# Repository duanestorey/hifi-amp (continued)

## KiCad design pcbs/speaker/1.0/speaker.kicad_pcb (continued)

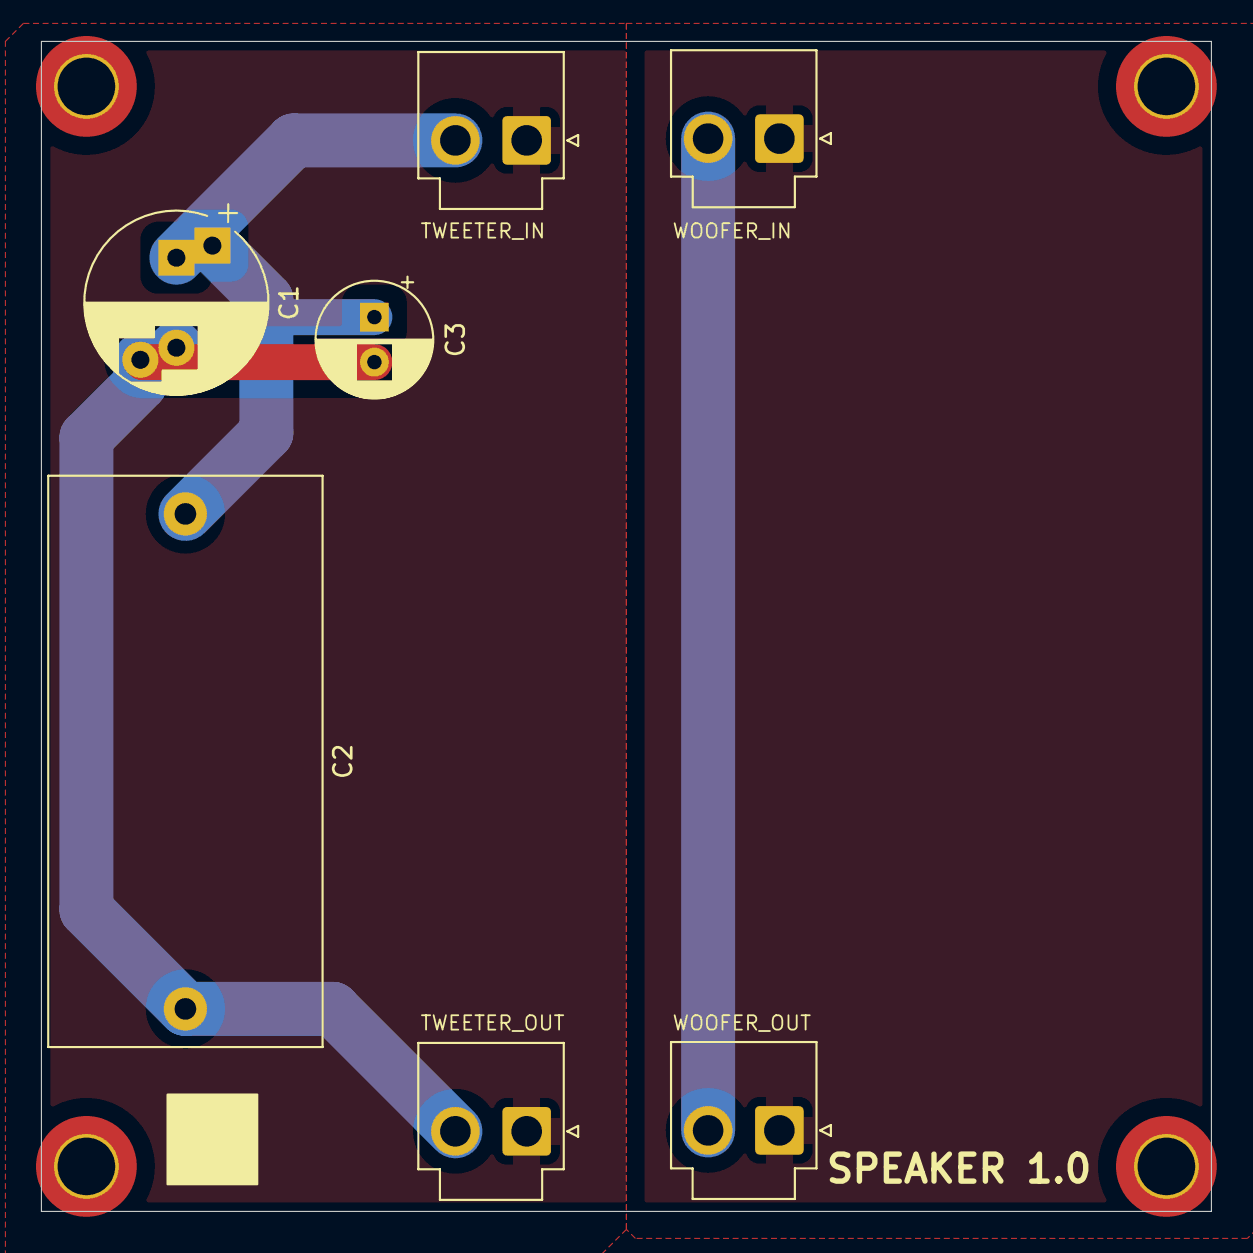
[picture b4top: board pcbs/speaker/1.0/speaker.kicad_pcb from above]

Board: 2 copper layers, 65.0 x 65.0 mm, 11 parts (0 on the bottom side), 5 nets.

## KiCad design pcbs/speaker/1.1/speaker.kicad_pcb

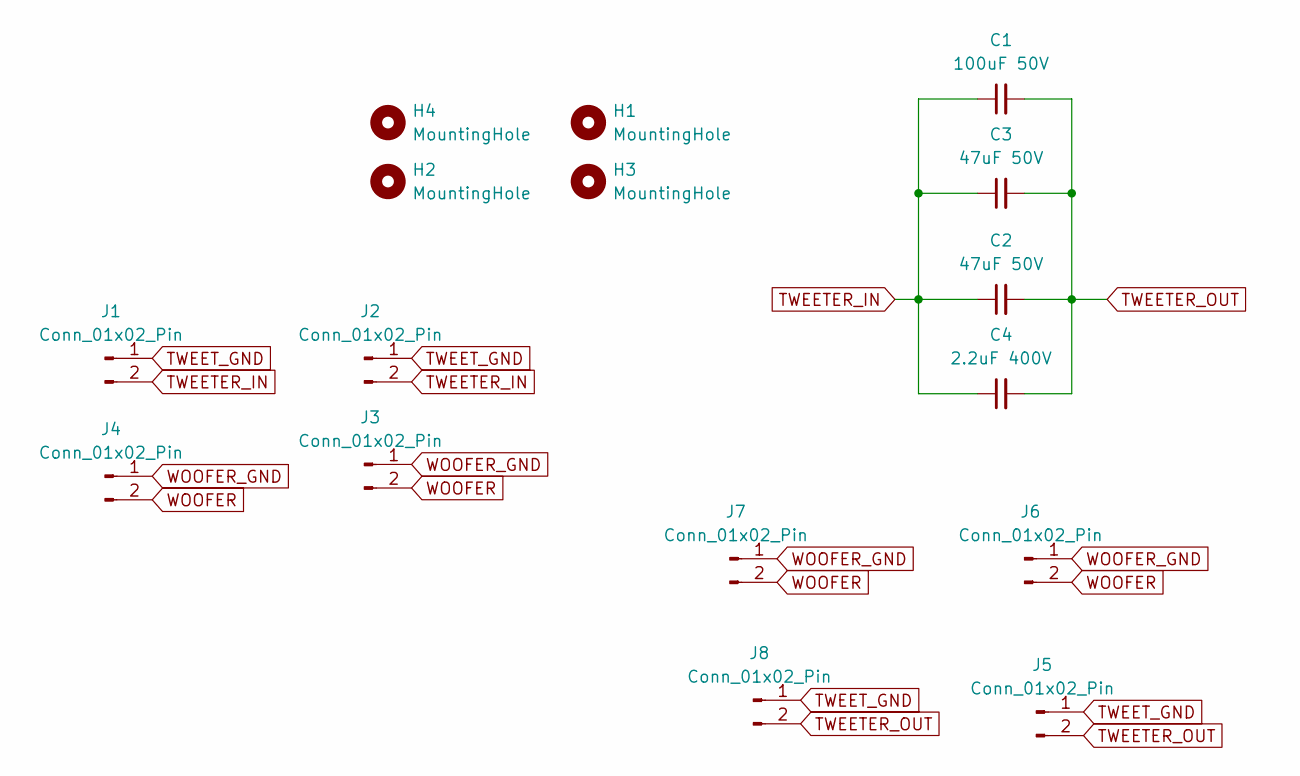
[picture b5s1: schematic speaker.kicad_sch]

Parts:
C1: 100uF 50V; CP_Radial_D12.5mm_P7.50mm
C2, C3: 47uF 50V; CP_Radial_D10.0mm_P5.00mm_P7.50mm
C4: 2.2uF 400V; C_Rect_L31.5mm_W15.0mm_P27.50mm_MKS4
H1, H2, H3, H4: MountingHole; MountingHole_3.2mm_M3_DIN965_Pad_TopBottom
J1, J4, J5, J6: Conn_01x02_Pin; TerminalBlock_Phoenix_PT-1,5-2-5.0-H_1x02_P5.00mm_Horizontal
J2, J3, J7, J8: Conn_01x02_Pin; JST_VH_B2P-VH-B_1x02_P3.96mm_Vertical

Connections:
TWEETER_IN: C1.1, C2.1, C3.1, C4.1, J1.2, J2.2
TWEETER_OUT: C1.2, C2.2, C3.2, C4.2, J5.2, J8.2
TWEET_GND: J1.1, J2.1, J5.1, J8.1
WOOFER: J3.2, J4.2, J6.2, J7.2
WOOFER_GND: J3.1, J4.1, J6.1, J7.1

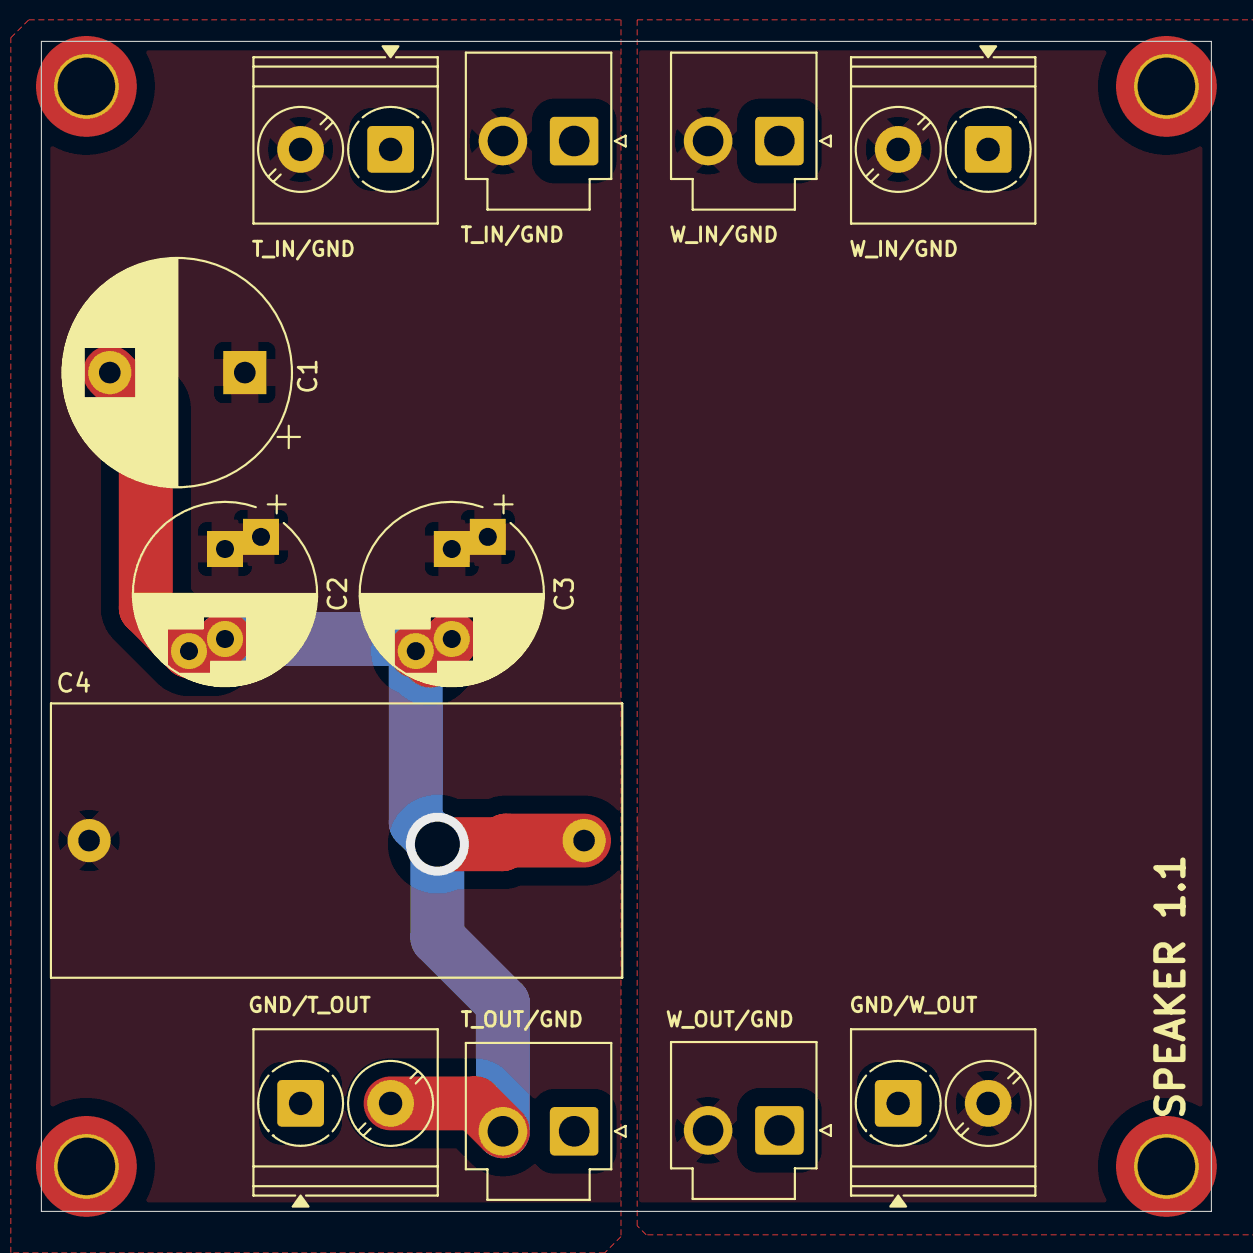
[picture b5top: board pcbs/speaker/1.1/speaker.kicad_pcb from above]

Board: 2 copper layers, 65.0 x 65.0 mm, 16 parts (0 on the bottom side), 5 nets.

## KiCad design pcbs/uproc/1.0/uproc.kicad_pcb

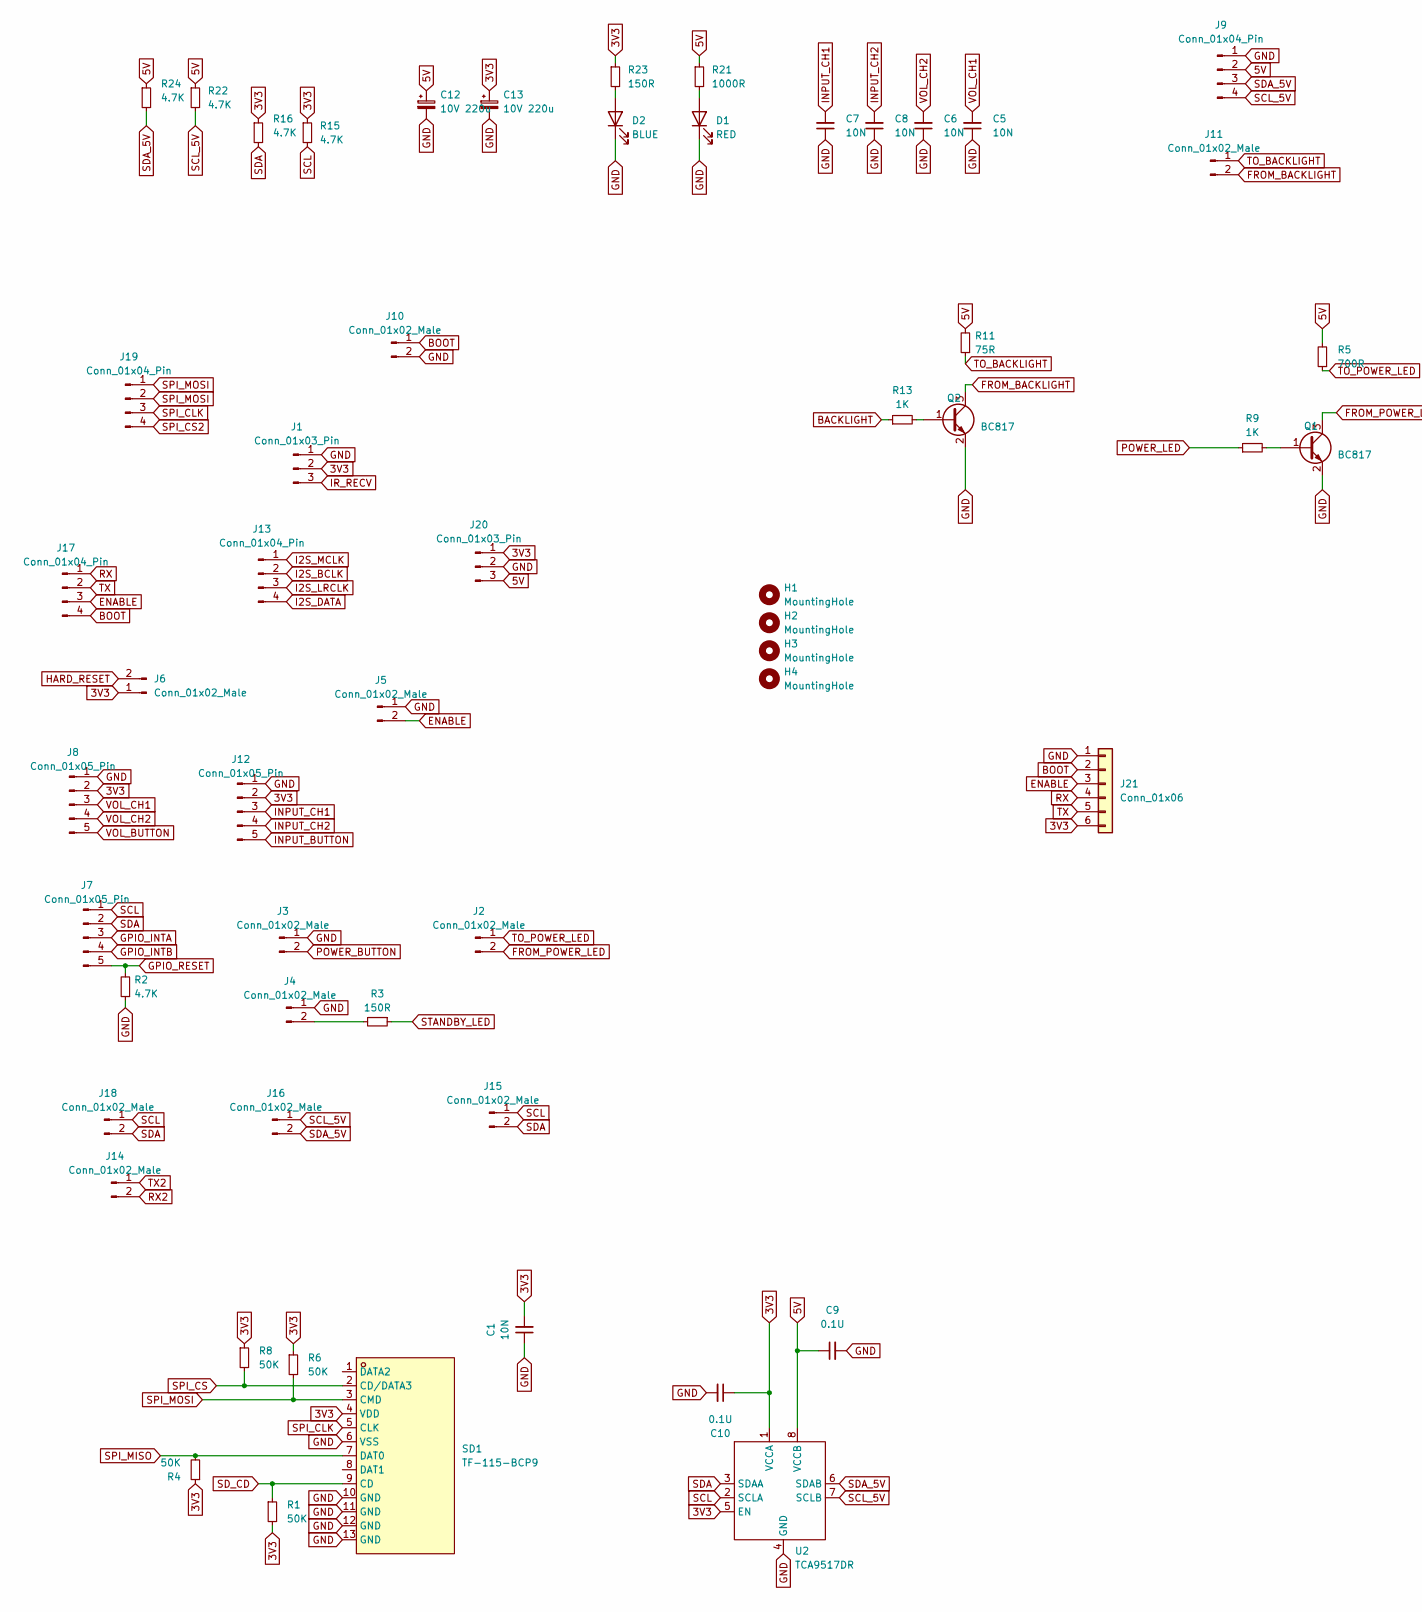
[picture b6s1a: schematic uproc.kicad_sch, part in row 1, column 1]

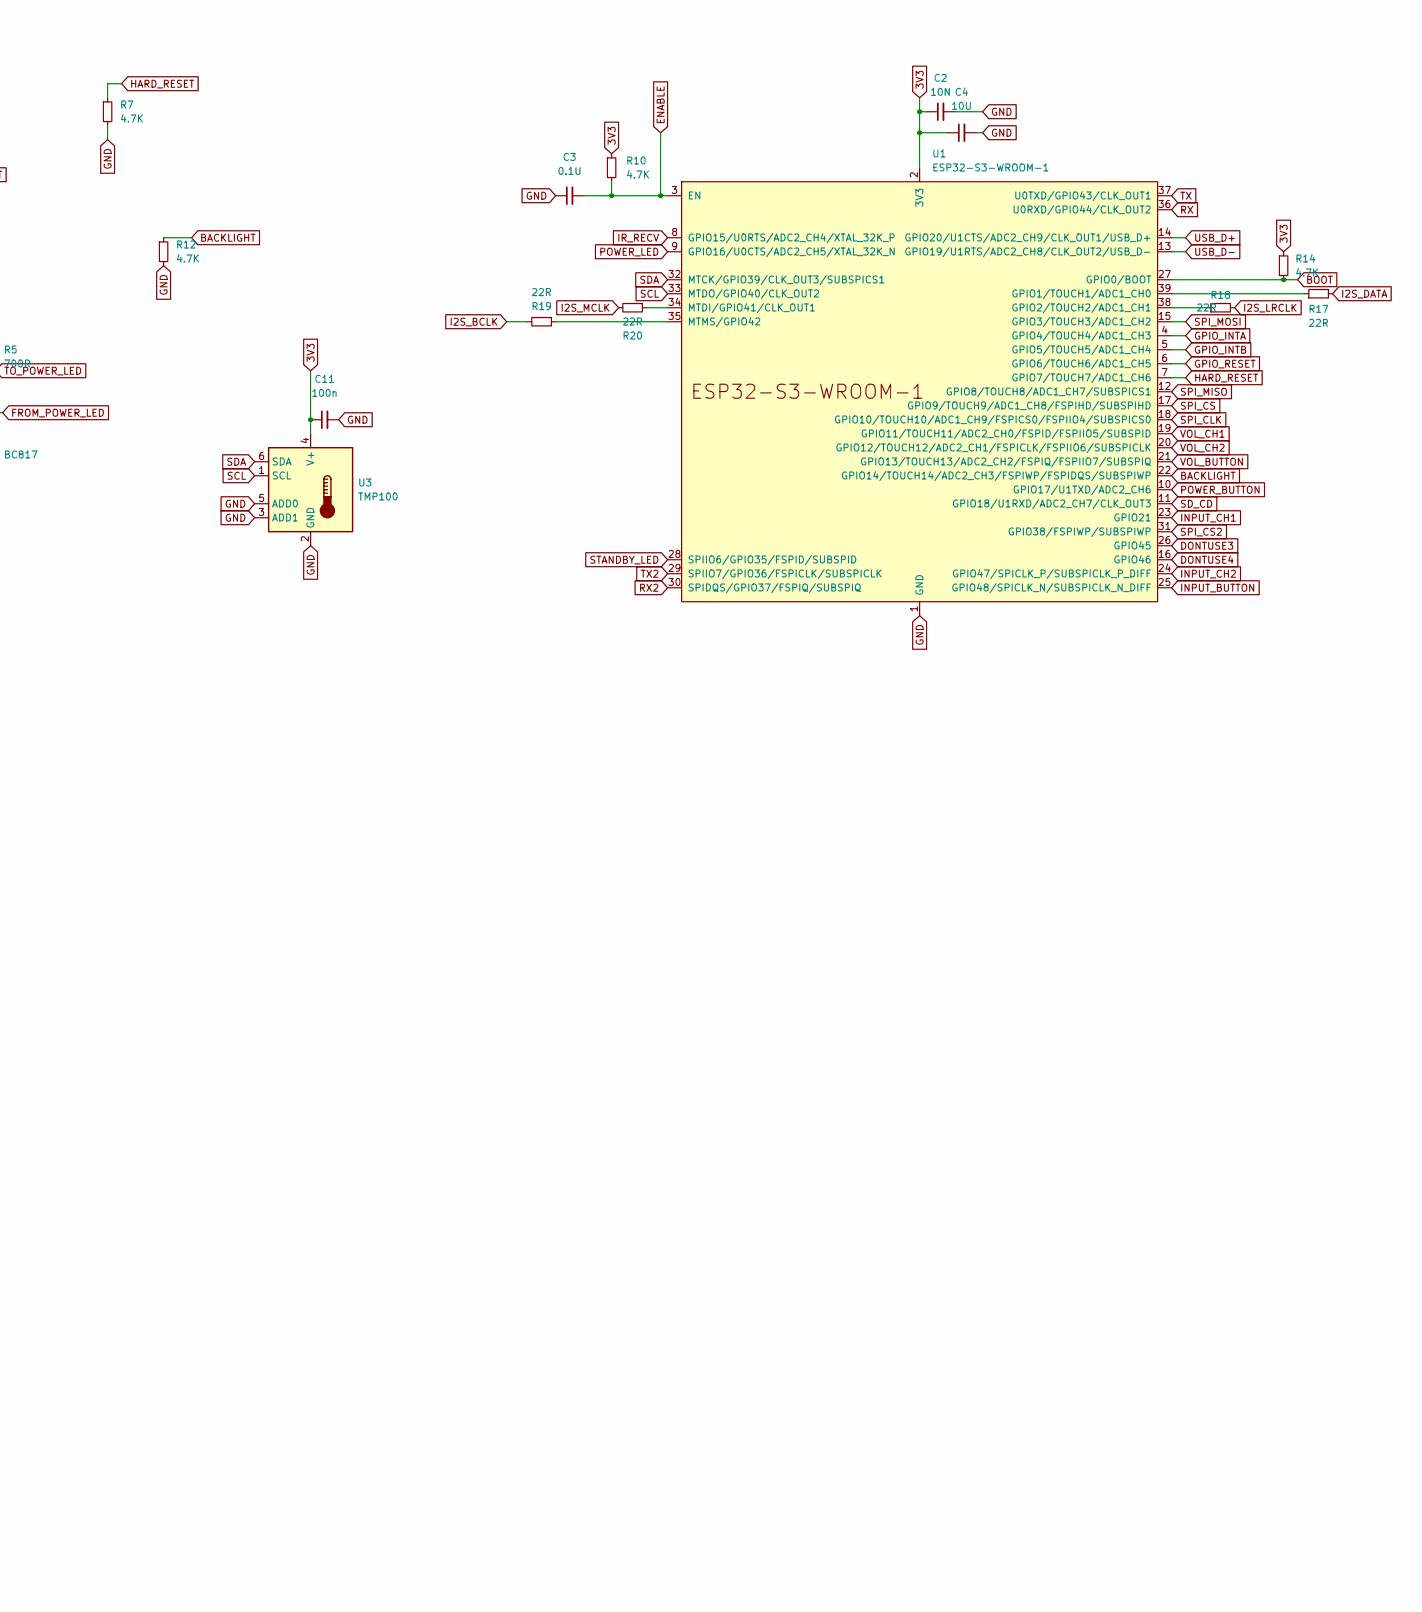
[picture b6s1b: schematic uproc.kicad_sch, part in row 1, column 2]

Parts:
C1, C2: 10N; C_0805_2012Metric_Pad1.18x1.45mm_HandSolder
C3, C9, C10: 0.1U; C_0805_2012Metric_Pad1.18x1.45mm_HandSolder
C4: 10U; C_1206_3216Metric_Pad1.33x1.80mm_HandSolder
C5, C6, C7, C8: 10N; C_0603_1608Metric_Pad1.08x0.95mm_HandSolder
C11: 100n; C_0805_2012Metric_Pad1.18x1.45mm_HandSolder
C12, C13: 10V 220u; CP_Radial_D6.3mm_P2.50mm
D1: RED; LED_0603_1608Metric; LCSC XL-1608UBC-04
D2: BLUE; LED_0603_1608Metric; LCSC NCD0603R1
H1, H2, H3, H4: MountingHole; MountingHole_3.2mm_M3_DIN965_Pad_TopOnly
J1, J20: Conn_01x03_Pin; JST_PH_B3B-PH-K_1x03_P2.00mm_Vertical
J2, J3, J4, J5, J11, J14, J15, J16, J18: Conn_01x02_Male; JST_PH_B2B-PH-K_1x02_P2.00mm_Vertical
J6, J10: Conn_01x02_Male; PinHeader_1x02_P2.54mm_Vertical
J7, J8, J12: Conn_01x05_Pin; JST_PH_B5B-PH-K_1x05_P2.00mm_Vertical
J9, J13, J17, J19: Conn_01x04_Pin; JST_PH_B4B-PH-K_1x04_P2.00mm_Vertical
J21: Conn_01x06; PinHeader_1x06_P2.54mm_Vertical
Q1, Q2: BC817; TSOT-23; Mouser 637-BC817K-40
R1, R4, R6, R8: 50K; R_0603_1608Metric_Pad0.98x0.95mm_HandSolder
R2, R7, R10, R12, R14, R15, R16, R22, R24: 4.7K; R_0603_1608Metric_Pad0.98x0.95mm_HandSolder
R3, R23: 150R; R_0603_1608Metric_Pad0.98x0.95mm_HandSolder
R5: 700R; R_0603_1608Metric_Pad0.98x0.95mm_HandSolder
R9, R13: 1K; R_0603_1608Metric_Pad0.98x0.95mm_HandSolder
R11: 75R; R_0603_1608Metric_Pad0.98x0.95mm_HandSolder
R17, R18, R19, R20: 22R; R_0603_1608Metric; Mouser 603-RT0805FRE0722RL
R21: 1000R; R_0603_1608Metric_Pad0.98x0.95mm_HandSolder
SD1: TF-115-BCP9; TF-SMD_TF-115-BCP9; LCSC Part C720505
U1: ESP32-S3-WROOM-1
U2: TCA9517DR; SOIC-8_3.9x4.9mm_P1.27mm; Mouser 595-TCA9517DR
U3: TMP100; SOT-23-6

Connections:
3V3: C1.2, C2.1, C4.1, C10.1, C11.1, C13.1, J1.2, J6.1, J8.2, J12.2, J20.1, J21.6, R1.2, R4.1, R6.1, R8.1, R10.1, R14.1, R15.1, R16.1, R23.1, SD1.4 (VDD), U1.2 (3V3), U2.1 (VCCA), U2.5 (EN), U3.4 (V+)
5V: C9.1, C12.1, J9.2, J20.3, R5.2, R11.2, R21.1, R22.1, R24.1, U2.8 (VCCB)
BACKLIGHT: R12.1, R13.1, U1.22 (GPIO14/TOUCH14/ADC2_CH3/FSPIWP/FSPIDQS/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)
BOOT: J10.1, J17.4, J21.2, R14.2, U1.27 (GPIO0/BOOT)
DONTUSE3: U1.26 (GPIO45)
DONTUSE4: U1.16 (GPIO46)
ENABLE: C3.2, J5.2, J17.3, J21.3, R10.2, U1.3 (EN)
FROM_BACKLIGHT: J11.2, Q2.3 (C)
FROM_POWER_LED: J2.2, Q1.3 (C)
GND: C1.1, C2.2, C3.1, C4.2, C5.1, C6.1, C7.1, C8.1, C9.2, C10.2, C11.2, C12.2, C13.2, D1.1 (K), D2.1 (K), J1.1, J3.1, J4.1, J5.1, J8.1, J9.1, J10.2, J12.1, J20.2, J21.1, Q1.2 (E), Q2.2 (E), R2.1, R7.2, R12.2, SD1.6 (VSS), SD1.10 (GND), SD1.11 (GND), SD1.12 (GND), SD1.13 (GND), U1.1 (GND), U1.40 (GND), U1.41 (GND), U2.4 (GND), U3.2 (GND), U3.3 (ADD1), U3.5 (ADD0)
GPIO_INTA: J7.3, U1.4 (GPIO4/TOUCH4/ADC1_CH3)
GPIO_INTB: J7.4, U1.5 (GPIO5/TOUCH5/ADC1_CH4)
GPIO_RESET: J7.5, R2.2, U1.6 (GPIO6/TOUCH6/ADC1_CH5)
HARD_RESET: J6.2, R7.1, U1.7 (GPIO7/TOUCH7/ADC1_CH6)
I2S_BCLK: J13.2, R19.2
I2S_DATA: J13.4, R17.2
I2S_LRCLK: J13.3, R18.2
I2S_MCLK: J13.1, R20.2
INPUT_BUTTON: J12.5, U1.25 (GPIO48/SPICLK_N/SUBSPICLK_N_DIFF)
INPUT_CH1: C7.2, J12.3, U1.23 (GPIO21)
INPUT_CH2: C8.2, J12.4, U1.24 (GPIO47/SPICLK_P/SUBSPICLK_P_DIFF)
IR_RECV: J1.3, U1.8 (GPIO15/U0RTS/ADC2_CH4/XTAL_32K_P)
unnamed: D1.2 (A), R21.2
unnamed: D2.2 (A), R23.2
unnamed: J4.2, R3.2
unnamed: Q1.1 (B), R9.2
unnamed: Q2.1 (B), R13.2
unnamed: R17.1, U1.39 (GPIO1/TOUCH1/ADC1_CH0)
unnamed: R18.1, U1.38 (GPIO2/TOUCH2/ADC1_CH1)
unnamed: R20.1, U1.34 (MTDI/GPIO41/CLK_OUT1)
unnamed: R19.1, U1.35 (MTMS/GPIO42)
POWER_BUTTON: J3.2, U1.10 (GPIO17/U1TXD/ADC2_CH6)
POWER_LED: R9.1, U1.9 (GPIO16/U0CTS/ADC2_CH5/XTAL_32K_N)
RX: J17.1, J21.4, U1.36 (U0RXD/GPIO44/CLK_OUT2)
RX2: J14.2, U1.30 (SPIDQS/GPIO37/FSPIQ/SUBSPIQ)
SCL: J7.1, J15.1, J18.1, R15.2, U1.33 (MTDO/GPIO40/CLK_OUT2), U2.2 (SCLA), U3.1 (SCL)
SCL_5V: J9.4, J16.1, R22.2, U2.7 (SCLB)
SDA: J7.2, J15.2, J18.2, R16.2, U1.32 (MTCK/GPIO39/CLK_OUT3/SUBSPICS1), U2.3 (SDAA), U3.6 (SDA)
SDA_5V: J9.3, J16.2, R24.2, U2.6 (SDAB)
SD_CD: R1.1, SD1.9 (CD), U1.11 (GPIO18/U1RXD/ADC2_CH7/CLK_OUT3)
SPI_CLK: J19.3, SD1.5 (CLK), U1.18 (GPIO10/TOUCH10/ADC1_CH9/FSPICS0/FSPIIO4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)
SPI_CS: R8.2, SD1.2 (CD/DATA3), U1.17 (GPIO9/TOUCH9/ADC1_CH8/FSPIHD/SUBSPIHD)
SPI_CS2: J19.4, U1.31 (GPIO38/FSPIWP/SUBSPIWP)
SPI_MISO: R4.2, SD1.7 (DAT0), U1.12 (GPIO8/TOUCH8/ADC1_CH7/SUBSPICS1)
SPI_MOSI: J19.1, J19.2, R6.2, SD1.3 (CMD), U1.15 (GPIO3/TOUCH3/ADC1_CH2)
STANDBY_LED: R3.1, U1.28 (SPIIO6/GPIO35/FSPID/SUBSPID)
TO_BACKLIGHT: J11.1, R11.1
TO_POWER_LED: J2.1, R5.1
TX: J17.2, J21.5, U1.37 (U0TXD/GPIO43/CLK_OUT1)
TX2: J14.1, U1.29 (SPIIO7/GPIO36/FSPICLK/SUBSPICLK)
USB_D+: U1.14 (GPIO20/U1CTS/ADC2_CH9/CLK_OUT1/USB_D+)
USB_D-: U1.13 (GPIO19/U1RTS/ADC2_CH8/CLK_OUT2/USB_D-)
VOL_BUTTON: J8.5, U1.21 (GPIO13/TOUCH13/ADC2_CH2/FSPIQ/FSPIIO7/S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)
VOL_CH1: C5.2, J8.3, U1.19 (GPIO11/TOUCH11/ADC2_CH0/FSPID/FSPIIO5/S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)
VOL_CH2: C6.2, J8.4, U1.20 (GPIO12/TOUCH12/ADC2_CH1/FSPICLK/FSPIIO6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)

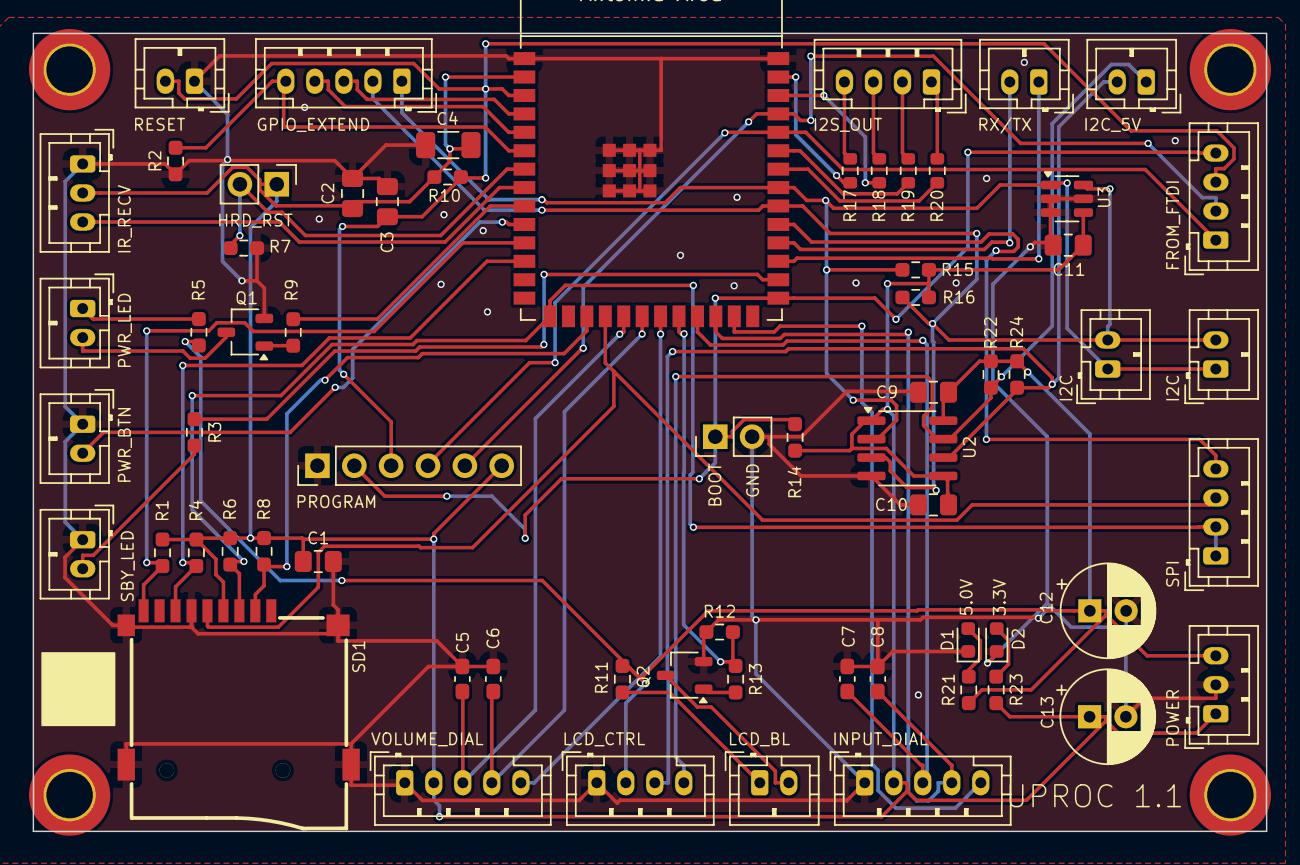
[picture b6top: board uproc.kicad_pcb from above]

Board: 2 copper layers, 85.0 x 55.0 mm, 70 parts (0 on the bottom side), 51 nets.
